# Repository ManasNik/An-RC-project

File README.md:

# **An RC car project**
This is a work in progress personal project that I started with a goal of building an RC car from scratch with an IMU based steering controller imitating real life steering action and to gain experience with STM32 microcontrollers. My initial goal for this project is to complete the basic functioning of the car and steering control. I have planned and I am planning to add more features in the future such as controls to adjust certain parameters to affect the handling of the car, telemetry, lap time counter and even a camera to get a First Person View(FPV)!

# **Current status**

Hardware:
- The car prototype is almost complete. I designed a simple prototype PCB to mount the off-the-shelf modules that I previously tested on the breadboard. The layout is intentionally minimal to reduce cost, keep complexity low, and allow the modules to be reused in future projects.
- Added extra capacitors on the PCB to suppress electrical noise generated by the motors on the power rails.
- The car is powered by a 600 mAh 25C LiPo battery.
- The controller circuit is still under development on the breadboard. I’m currently testing different features, tuning behavior, and iterating on the design.

Software:
- Developed a NRF24L01 driver for wireless communication between the controller and the car.
- Developed a driver for the MPU6050 IMU. Using a complementary filter to combine accelerometer and gyroscope data for accurate steering-angle estimation.
- Implemented the core firmware for basic motion control (forward, reverse, left, right).

# **Development journey**
The following section documents my project journey in detail from the start to the current stage.

## **Components used(so far)**
TB6612FNG x2   
STM32F103CBT6 x2  
Potentiometers for intial testing x2  
NRF24L01 x2
MPU6050 x1

## **The initial breadboard circuit**

(It's a mess of wires!)

I started my project by testing individual motors with the driver and eventually wired them all together. I initially tested using the STM32F446RE Nucleo board since it was readily available with me then. Obviously it's an overkill for this project and so I decided to use the STM32F103CBT6, which is still a powerful MCU for this project but leaves me headroom for adding interesting features later on in the future.
I used two potentiometers - one for speed control(throttle) and the other for steering control. This is the point I learned about DMA(Direct Memory Access) as it was needed to process the two ADC channels efficiently. Additionally I used the built-in button on the Nucleo board to enable/disable reverse under a specified speed. My idea is to implement the reverse button on the steering wheel controller later on in the future to engage/disengage reverse like in an F1 car! It has to be noted that the controller is not designed or involved in this initial setup - This is a hardwired test. 

I wanted to design a simple platform to hold my motors (the chassis) and small wheels to fit my desired form factor. I decided to design and 3D print my own design.

**Chassis design**

**Wheel design**

**The outcome of the design**

(Placed a mouse there for comparison!)

# **Implementing remote control**
  
(The car circuit is on the left and the controller on the right)

In this stage of the project I decided to add the remote control using two NRF24L01 modules - one on the car and one in the controller. To develop the driver for communicating with this module, I followed a YouTube tutorial and the NRF24l01 datasheet. This is the first time I wrote a driver by manipulating low level registers -  a great learning experience indeed! Once the driver development was done, it was time to test it. I shifted the two potentiometers and the reverse button to one of the two STM32F103CBT6 boards I will be using for the rest of this project and connected the NRF24L01 module via SPI. Similarly, I shifted the motor drivers to the other STM32F103CBT6 board and connected the other NRF24L01 module via SPI. I was now able to control the car through wireless communication!

# **Implementing IMU based steering control**
I chose the cheap and easily available MPU6050 Inertial Measurement Unit(IMU) module and developed a driver to communicate with it using I2C. After I confirmed I was receiving the gyroscope and accelerometer data from the IMU, I started working on the code to process it. I used a simple Exponential Moving Average (EMA) filter to smoothen out some noise from the readings, and used a complementary filter to combine the readings of both the gyroscope and the accelerometer to improve the steering angle estimation. 

I scaled the steering angle estimation and computed a steering amount to add or subtract from the PWM control values to change the motor speeds according to the direction of the steering. The car doesn't have a deciated mechanical steering system and the steering rotation is achieved by varying the speeds on each side of the car. To turn left, the speed is reduced on the left side and increased on the right side and vice versa.

# **PCB Design** 
I designed a simple 2-layered PCB to transfer the breadboard circuit onto the 3d printed car platform I previously designed. I can now test the car on the ground with the control logic I developed in software and fine tune it to improve the handling characteristics. I intentionally made the PCB design simple by using footprints for female/socket headers spaced appropriately to insert the off-the-shelf modules. This reduced the complexity of the design, made it cheaper to manufacture and made it possible to resue the modules for other projects. 

**Schematic**

**PCB design**

Final PCB

This was my first time designing a PCB on my own and ordering it. Obviously I made mistakes!
- I forgot to include capacitors in the design to reduce the noise on the power lines, since the brushed DC motors cause electrical noise due to brush-commutator sparking. This noise interfered a lot with the NRF24L01 module making it lose connection with the controller. I greatly reduced this later by soldering electrolytic and ceramic capacitors near the motor termianls and power supply pins of the modules.
- I should've taken extra care to provide a stable power supply directly to the NRF24L01 module instead of supplying it from the 3.3V pin of the STM32 module.
 
# **What's next?**
(This section will be updated from time to time till the completion of the project)
- The car is pretty quick on the ground and coasts to a stop instead of stopping quickly. I am working on a braking logic to slow down the car on command. The brake paddle will be one of the two paddles I'm planning to add behind my steering wheel controller with the other one being the throttle paddle. I will develop the logic in such a way that the user can fine tune the characteristics of the car according to their preference.
- I'm planning to add a Time-Of-Flight sensor at the front of the car to detect obstacles ahead to avoid a head-on collision when the controller connection is lost - A backup safety feature.
- I will develop a simple pit limiter making use of a hall sensor to measure wheel RPM to enable closed loop speed control. The hall sensor will also be crucial to avoid unwanted movement of the car due to steering movement even when no throttle is applied at rest.

This project for me isn't just about building an RC car - it's a fun learning experience that will help me dive deep into complete embedded system design from the ground up.

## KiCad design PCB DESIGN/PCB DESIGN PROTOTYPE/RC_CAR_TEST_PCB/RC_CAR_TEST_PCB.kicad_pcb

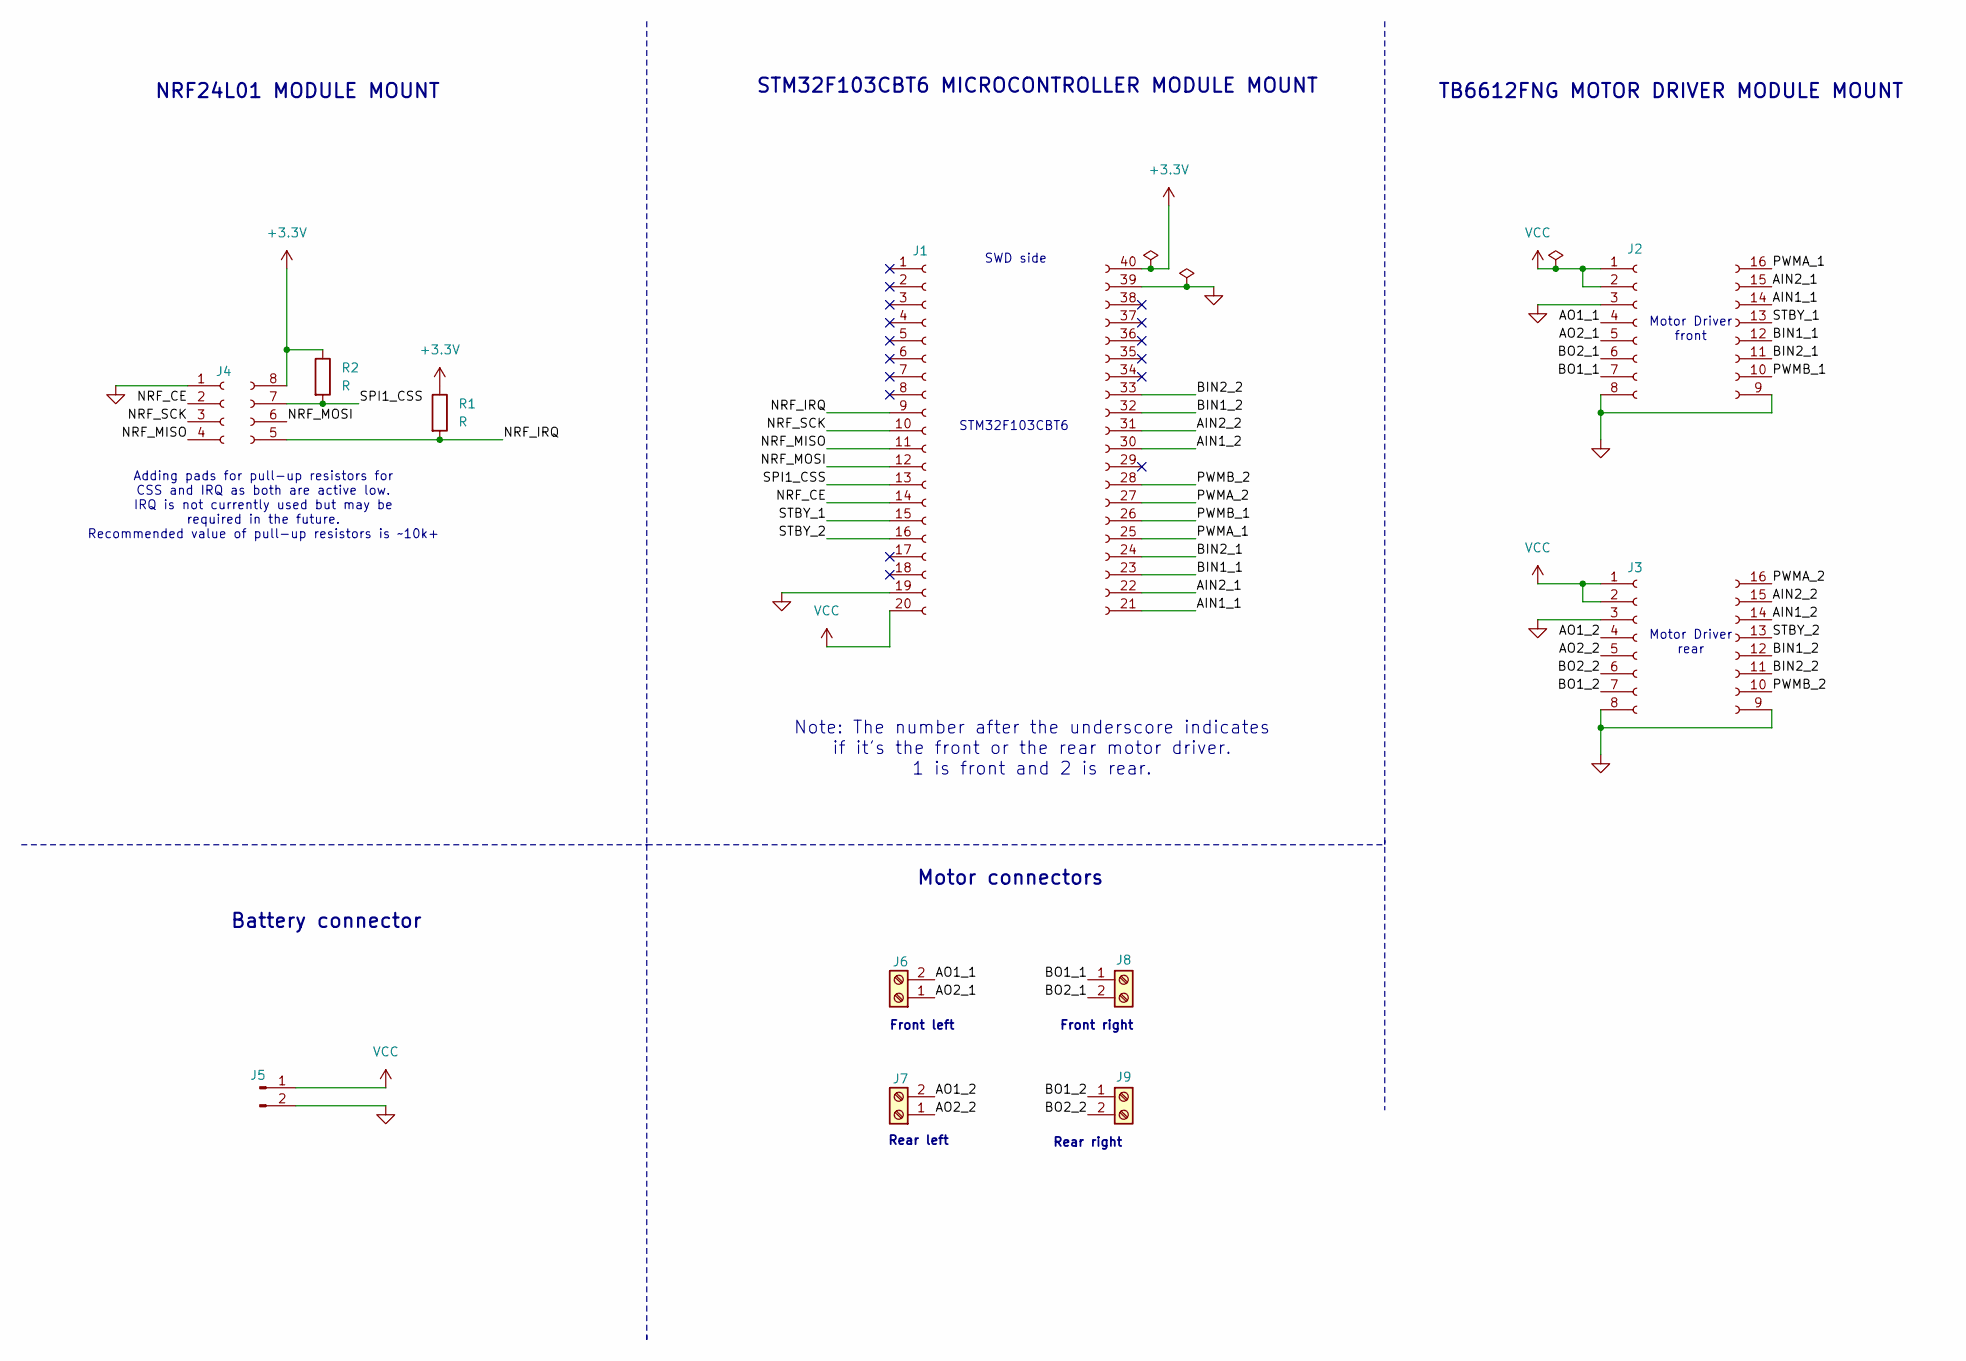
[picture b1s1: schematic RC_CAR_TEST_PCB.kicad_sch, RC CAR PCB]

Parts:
J1: Conn_02x20_Socket; Bluepill
J2, J3: Conn_02x08_Socket; TB6612FNG
J4: Conn_01x04_Socket; NRF24L01
J5: Conn_01x02_Pin; JST_VH_B2P-VH_1x02_P3.96mm_Vertical
J6, J7, J8, J9: Screw_Terminal_01x02; TerminalBlock_4Ucon_1x02_P3.50mm_Horizontal
R1, R2: R; R_Axial_DIN0204_L3.6mm_D1.6mm_P5.08mm_Horizontal

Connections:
+3.3V: J1.40 (Pin_20), J4.8 (Pin_4), R1.1, R2.1
/AIN1_1: J1.21 (Pin_1), J2.14 (Pin_3)
/AIN1_2: J1.30 (Pin_10), J3.14 (Pin_3)
/AIN2_1: J1.22 (Pin_2), J2.15 (Pin_2)
/AIN2_2: J1.31 (Pin_11), J3.15 (Pin_2)
/AO1_1: J2.4, J6.2
/AO1_2: J3.4, J7.2
/AO2_1: J2.5, J6.1
/AO2_2: J3.5, J7.1
/BIN1_1: J1.23 (Pin_3), J2.12 (Pin_5)
/BIN1_2: J1.32 (Pin_12), J3.12 (Pin_5)
/BIN2_1: J1.24 (Pin_4), J2.11 (Pin_6)
/BIN2_2: J1.33 (Pin_13), J3.11 (Pin_6)
/BO1_1: J2.7, J8.1
/BO1_2: J3.7, J9.1
/BO2_1: J2.6, J8.2
/BO2_2: J3.6, J9.2
/NRF_CE: J1.14, J4.2
/NRF_IRQ: J1.9, J4.5 (Pin_1), R1.2
/NRF_MISO: J1.11, J4.4
/NRF_MOSI: J1.12, J4.6 (Pin_2)
/NRF_SCK: J1.10, J4.3
/PWMA_1: J1.25 (Pin_5), J2.16 (Pin_1)
/PWMA_2: J1.27 (Pin_7), J3.16 (Pin_1)
/PWMB_1: J1.26 (Pin_6), J2.10 (Pin_7)
/PWMB_2: J1.28 (Pin_8), J3.10 (Pin_7)
/SPI1_CSS: J1.13, J4.7 (Pin_3), R2.2
/STBY_1: J1.15, J2.13 (Pin_4)
/STBY_2: J1.16, J3.13 (Pin_4)
GND: J1.19, J1.39 (Pin_19), J2.3, J2.8, J2.9 (Pin_8), J3.3, J3.8, J3.9 (Pin_8), J4.1, J5.2
VCC: J1.20, J2.1, J2.2, J3.1, J3.2, J5.1

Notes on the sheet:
Front left
STM32F103CBT6
TB6612FNG MOTOR DRIVER MODULE MOUNT
Motor connectors
Adding pads for pull-up resistors for CSS and IRQ as both are active low. IRQ is not currently used but may be required in the future. Recommended value of pull-up resistors is ~10k+
Front right
Note: The number after the underscore indicates if it's the front or the rear motor driver. 1 is front and 2 is rear.
Rear left
Rear right
NRF24L01 MODULE MOUNT
Motor Driver front
SWD side
STM32F103CBT6 MICROCONTROLLER MODULE MOUNT
Motor Driver rear
Battery connector

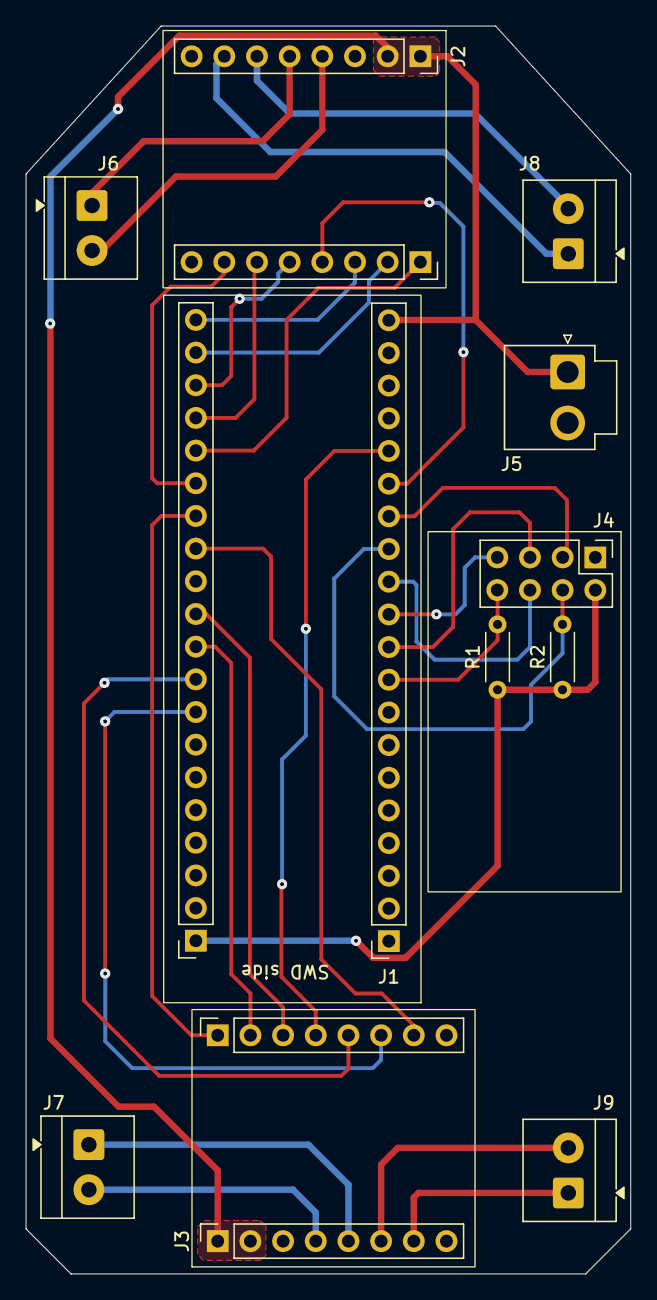
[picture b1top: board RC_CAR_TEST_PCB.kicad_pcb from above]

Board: 2 copper layers, 47.0 x 97.0 mm, 11 parts (0 on the bottom side), 31 nets.

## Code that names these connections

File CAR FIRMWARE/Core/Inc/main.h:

/* USER CODE BEGIN Header */
/**
  ******************************************************************************
  * @file           : main.h
  * @brief          : Header for main.c file.
  *                   This file contains the common defines of the application.
  ******************************************************************************
  * @attention
  *
  * Copyright (c) 2025 STMicroelectronics.
  * All rights reserved.
  *
  * This software is licensed under terms that can be found in the LICENSE file
  * in the root directory of this software component.
  * If no LICENSE file comes with this software, it is provided AS-IS.
  *
  ******************************************************************************
  */
/* USER CODE END Header */

/* Define to prevent recursive inclusion -------------------------------------*/
#ifndef __MAIN_H
#define __MAIN_H

#ifdef __cplusplus
extern "C" {
#endif

/* Includes ------------------------------------------------------------------*/
#include "stm32f1xx_hal.h"

/* Private includes ----------------------------------------------------------*/
/* USER CODE BEGIN Includes */

/* USER CODE END Includes */

/* Exported types ------------------------------------------------------------*/
/* USER CODE BEGIN ET */

/* USER CODE END ET */

/* Exported constants --------------------------------------------------------*/
/* USER CODE BEGIN EC */

/* USER CODE END EC */

/* Exported macro ------------------------------------------------------------*/
/* USER CODE BEGIN EM */

/* USER CODE END EM */

void HAL_TIM_MspPostInit(TIM_HandleTypeDef *htim);

/* Exported functions prototypes ---------------------------------------------*/
void Error_Handler(void);

/* USER CODE BEGIN EFP */

/* USER CODE END EFP */

/* Private defines -----------------------------------------------------------*/
#define CSS_Pin GPIO_PIN_0
#define CSS_GPIO_Port GPIOB
#define CE_Pin GPIO_PIN_1
#define CE_GPIO_Port GPIOB
#define LED_Pin GPIO_PIN_2
#define LED_GPIO_Port GPIOB
#define STBY_1_Pin GPIO_PIN_10
#define STBY_1_GPIO_Port GPIOB
#define STBY_2_Pin GPIO_PIN_11
#define STBY_2_GPIO_Port GPIOB
#define AIN1_1_Pin GPIO_PIN_12
#define AIN1_1_GPIO_Port GPIOB
#define AIN2_1_Pin GPIO_PIN_13
#define AIN2_1_GPIO_Port GPIOB
#define BIN1_1_Pin GPIO_PIN_14
#define BIN1_1_GPIO_Port GPIOB
#define BIN2_1_Pin GPIO_PIN_15
#define BIN2_1_GPIO_Port GPIOB
#define PWMA_1_Pin GPIO_PIN_8
#define PWMA_1_GPIO_Port GPIOA
#define PWMB_1_Pin GPIO_PIN_9
#define PWMB_1_GPIO_Port GPIOA
#define PWMA_2_Pin GPIO_PIN_10
#define PWMA_2_GPIO_Port GPIOA
#define PWMB_2_Pin GPIO_PIN_11
#define PWMB_2_GPIO_Port GPIOA
#define AIN1_2_Pin GPIO_PIN_15
#define AIN1_2_GPIO_Port GPIOA
#define AIN2_2_Pin GPIO_PIN_3
#define AIN2_2_GPIO_Port GPIOB
#define BIN1_2_Pin GPIO_PIN_4
#define BIN1_2_GPIO_Port GPIOB
#define BIN2_2_Pin GPIO_PIN_5
#define BIN2_2_GPIO_Port GPIOB

/* USER CODE BEGIN Private defines */

/* USER CODE END Private defines */

#ifdef __cplusplus
}
#endif

#endif /* __MAIN_H */

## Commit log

2025-07-17 Initial commit: Controller code
2025-07-17 Initial commit: Car code
2025-07-17 Inital commit: Car protoype design
2025-07-17 Added a README file
2025-07-18 Update README.md
    Added more info
2025-09-04 Developed MPU6050 driver and used the accelerometer values for steering
2025-09-04 Made my first PCB and the first for this project.
2025-12-03 Updates and progress
2025-12-03 Removed unwanted folders
2025-12-03 updated gitignore to prevent unwanted folders
2025-12-03 Update README with project status and future plans
    Expanded project details and current status, including hardware and software updates. Added sections on PCB design and future plans.
2025-12-04 Update README
    Added final PCB image and personal notes on design mistakes.
